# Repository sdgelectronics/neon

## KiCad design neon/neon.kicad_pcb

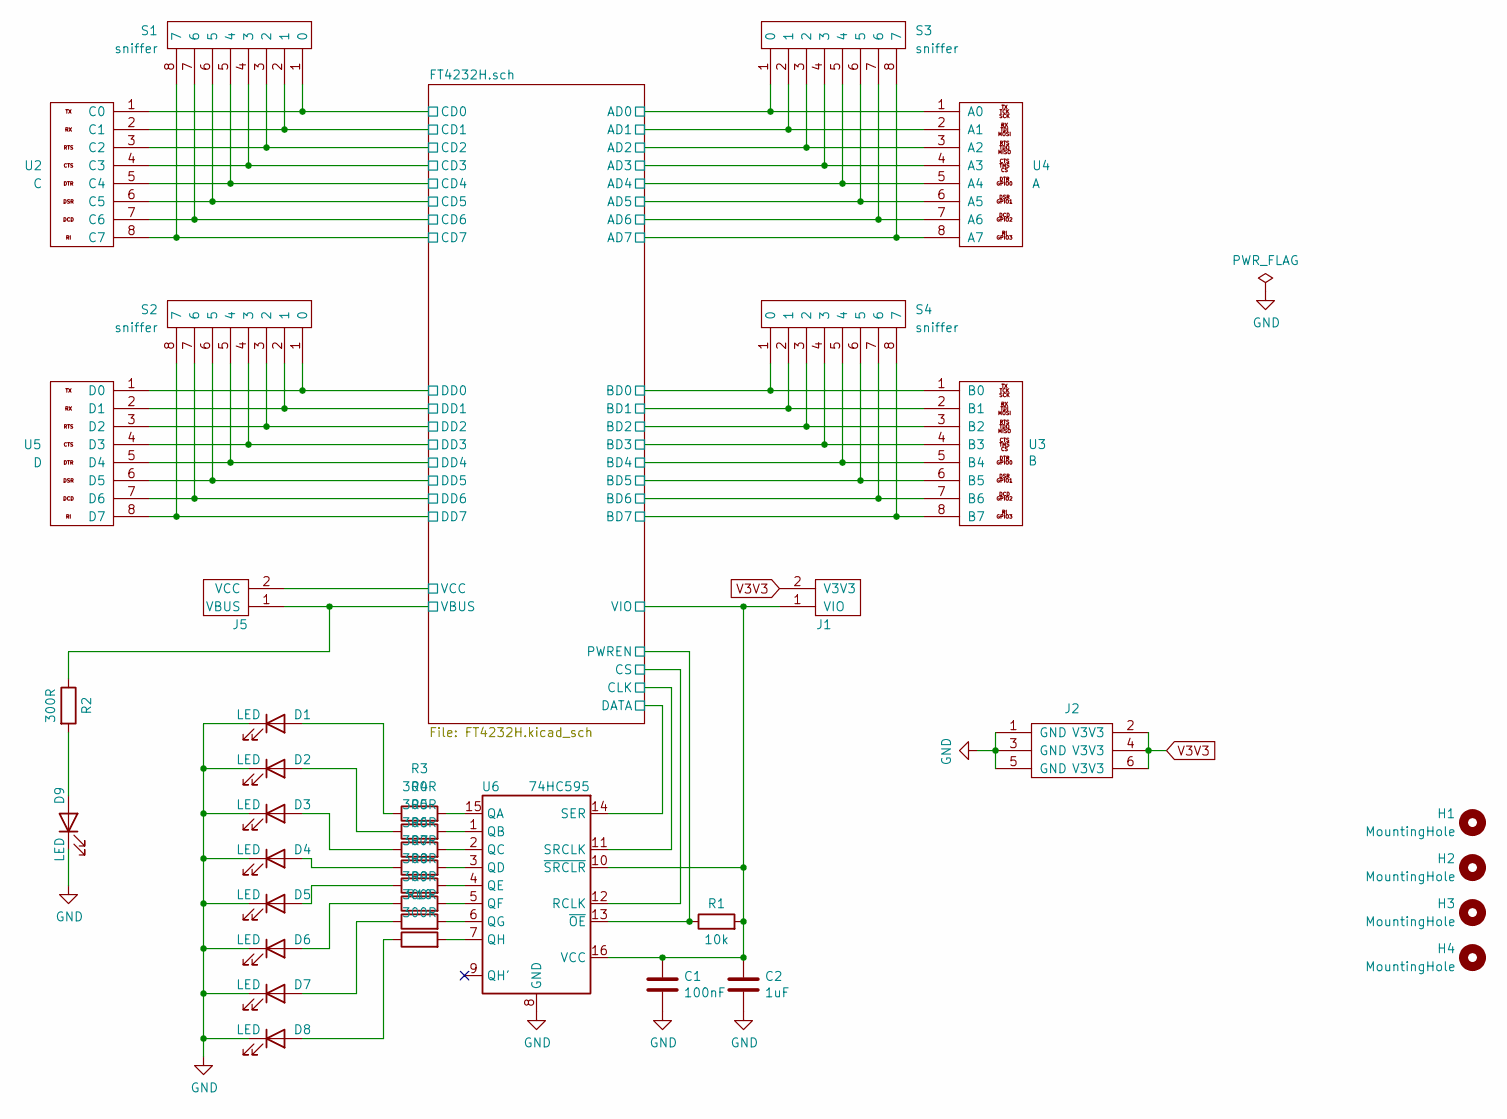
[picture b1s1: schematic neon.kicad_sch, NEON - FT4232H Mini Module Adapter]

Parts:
C1: 100nF; C_0805_2012Metric
C2: 1uF; C_0805_2012Metric
D1, D2, D3, D4, D5, D6, D7, D8, D9: LED; LED_0805_2012Metric
H1, H2, H3, H4: MountingHole; MountingHole_3.2mm_M3
J1: V3V3-VIO; PinHeader_1x02_P2.54mm_Vertical
J2: 3xV3V3-GND; PinHeader_2x03_P2.54mm_Vertical
J5: VBUS-VCC; PinHeader_1x02_P2.54mm_Vertical
R1: 10k; R_0805_2012Metric
R2: 300R; R_0805_2012Metric
R3, R4, R5, R6, R7, R8, R9, R10: 300R; R_0805_2012Metric_Pad1.20x1.40mm_HandSolder
S1, S2, S3, S4: sniffer; PinHeader_1x08_P2.54mm_Vertical
U2: C; PinHeader_1x08_P2.54mm_Vertical
U3: B; PinHeader_1x08_P2.54mm_Vertical
U4: A; PinHeader_1x08_P2.54mm_Vertical
U5: D; PinHeader_1x08_P2.54mm_Vertical
U6: 74HC595; SOIC-16_3.9x9.9mm_P1.27mm

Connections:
/AD0: S3.1 (0), U4.1 (A0); also elsewhere on the board
/AD1: S3.2 (1), U4.2 (A1); also elsewhere on the board
/AD2: S3.3 (2), U4.3 (A2); also elsewhere on the board
/AD3: S3.4 (3), U4.4 (A3); also elsewhere on the board
/AD4: S3.5 (4), U4.5 (A4); also elsewhere on the board
/AD5: S3.6 (5), U4.6 (A5); also elsewhere on the board
/AD6: S3.7 (6), U4.7 (A6); also elsewhere on the board
/AD7: S3.8 (7), U4.8 (A7); also elsewhere on the board
/BD0: S4.1 (0), U3.1 (B0); also elsewhere on the board
/BD1: S4.2 (1), U3.2 (B1); also elsewhere on the board
/BD2: S4.3 (2), U3.3 (B2); also elsewhere on the board
/BD3: S4.4 (3), U3.4 (B3); also elsewhere on the board
/BD4: S4.5 (4), U3.5 (B4); also elsewhere on the board
/BD5: S4.6 (5), U3.6 (B5); also elsewhere on the board
/BD6: S4.7 (6), U3.7 (B6); also elsewhere on the board
/BD7: S4.8 (7), U3.8 (B7); also elsewhere on the board
/CD0: S1.1 (0), U2.1 (C0); also elsewhere on the board
/CD1: S1.2 (1), U2.2 (C1); also elsewhere on the board
/CD2: S1.3 (2), U2.3 (C2); also elsewhere on the board
/CD3: S1.4 (3), U2.4 (C3); also elsewhere on the board
/CD4: S1.5 (4), U2.5 (C4); also elsewhere on the board
/CD5: S1.6 (5), U2.6 (C5); also elsewhere on the board
/CD6: S1.7 (6), U2.7 (C6); also elsewhere on the board
/CD7: S1.8 (7), U2.8 (C7); also elsewhere on the board
/CLK: U6.11 (SRCLK); also elsewhere on the board
/CS: U6.12 (RCLK); also elsewhere on the board
/DATA: U6.14 (SER); also elsewhere on the board
/DD0: S2.1 (0), U5.1 (D0); also elsewhere on the board
/DD1: S2.2 (1), U5.2 (D1); also elsewhere on the board
/DD2: S2.3 (2), U5.3 (D2); also elsewhere on the board
/DD3: S2.4 (3), U5.4 (D3); also elsewhere on the board
/DD4: S2.5 (4), U5.5 (D4); also elsewhere on the board
/DD5: S2.6 (5), U5.6 (D5); also elsewhere on the board
/DD6: S2.7 (6), U5.7 (D6); also elsewhere on the board
/DD7: S2.8 (7), U5.8 (D7); also elsewhere on the board
/PWREN: R1.1, U6.13 (~OE); also elsewhere on the board
/VBUS: J5.1 (VBUS), R2.1; also elsewhere on the board
/VCC: J5.2 (VCC); also elsewhere on the board
/VIO: C1.1, C2.1, J1.1 (VIO), R1.2, U6.10 (~SRCLR), U6.16 (VCC); also elsewhere on the board
GND: C1.2, C2.2, D1.1 (K), D2.1 (K), D3.1 (K), D4.1 (K), D5.1 (K), D6.1 (K), D7.1 (K), D8.1 (K), D9.1 (K), J2.1 (GND), J2.3 (GND), J2.5 (GND), U6.8 (GND); also elsewhere on the board
unnamed: D1.2 (A), R3.1
unnamed: D2.2 (A), R4.1
unnamed: D3.2 (A), R5.1
unnamed: D4.2 (A), R6.1
unnamed: D5.2 (A), R7.1
unnamed: D6.2 (A), R8.1
unnamed: D7.2 (A), R9.1
unnamed: D8.2 (A), R10.1
unnamed: D9.2 (A), R2.2
unnamed: R3.2, U6.15 (QA)
unnamed: R4.2, U6.1 (QB)
unnamed: R5.2, U6.2 (QC)
unnamed: R6.2, U6.3 (QD)
unnamed: R7.2, U6.4 (QE)
unnamed: R8.2, U6.5 (QF)
unnamed: R9.2, U6.6 (QG)
unnamed: R10.2, U6.7 (QH)
V3V3: J1.2 (V3V3), J2.2 (V3V3), J2.4 (V3V3), J2.6 (V3V3); also elsewhere on the board
no_connect_63: U6.9 (QH')

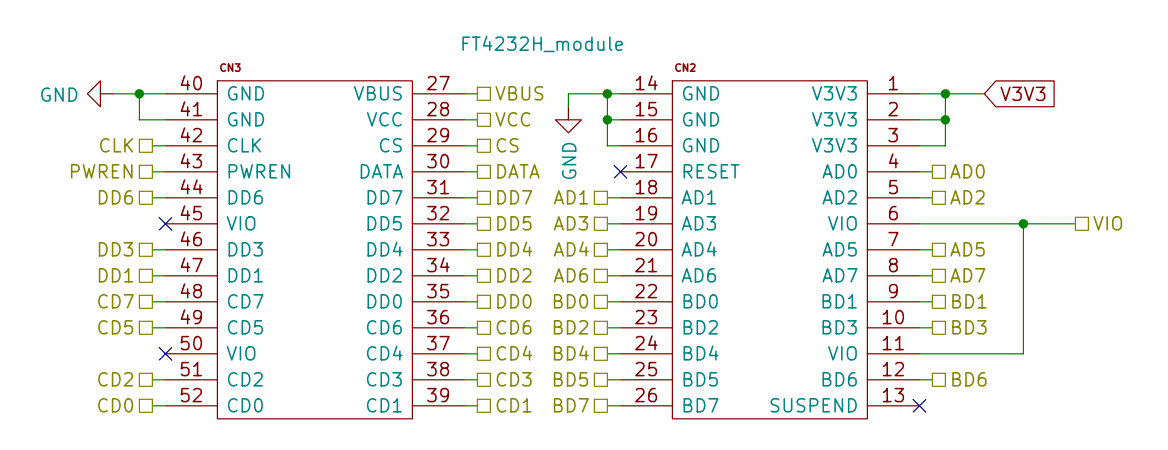
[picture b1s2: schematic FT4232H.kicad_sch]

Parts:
U1: FT4232H_module; FT4232H-MINI-MODULE-2

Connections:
/AD0: U1.4 (AD0); also elsewhere on the board
/AD1: U1.18 (AD1); also elsewhere on the board
/AD2: U1.5 (AD2); also elsewhere on the board
/AD3: U1.19 (AD3); also elsewhere on the board
/AD4: U1.20 (AD4); also elsewhere on the board
/AD5: U1.7 (AD5); also elsewhere on the board
/AD6: U1.21 (AD6); also elsewhere on the board
/AD7: U1.8 (AD7); also elsewhere on the board
/BD0: U1.22 (BD0); also elsewhere on the board
/BD1: U1.9 (BD1); also elsewhere on the board
/BD2: U1.23 (BD2); also elsewhere on the board
/BD3: U1.10 (BD3); also elsewhere on the board
/BD4: U1.24 (BD4); also elsewhere on the board
/BD5: U1.25 (BD5); also elsewhere on the board
/BD6: U1.12 (BD6); also elsewhere on the board
/BD7: U1.26 (BD7); also elsewhere on the board
/CD0: U1.52 (CD0); also elsewhere on the board
/CD1: U1.39 (CD1); also elsewhere on the board
/CD2: U1.51 (CD2); also elsewhere on the board
/CD3: U1.38 (CD3); also elsewhere on the board
/CD4: U1.37 (CD4); also elsewhere on the board
/CD5: U1.49 (CD5); also elsewhere on the board
/CD6: U1.36 (CD6); also elsewhere on the board
/CD7: U1.48 (CD7); also elsewhere on the board
/CLK: U1.42 (CLK); also elsewhere on the board
/CS: U1.29 (CS); also elsewhere on the board
/DATA: U1.30 (DATA); also elsewhere on the board
/DD0: U1.35 (DD0); also elsewhere on the board
/DD1: U1.47 (DD1); also elsewhere on the board
/DD2: U1.34 (DD2); also elsewhere on the board
/DD3: U1.46 (DD3); also elsewhere on the board
/DD4: U1.33 (DD4); also elsewhere on the board
/DD5: U1.32 (DD5); also elsewhere on the board
/DD6: U1.44 (DD6); also elsewhere on the board
/DD7: U1.31 (DD7); also elsewhere on the board
/PWREN: U1.43 (PWREN); also elsewhere on the board
/VBUS: U1.27 (VBUS); also elsewhere on the board
/VCC: U1.28 (VCC); also elsewhere on the board
/VIO: U1.6 (VIO), U1.11 (VIO); also elsewhere on the board
GND: U1.14 (GND), U1.15 (GND), U1.16 (GND), U1.40 (GND), U1.41 (GND); also elsewhere on the board
V3V3: U1.1 (V3V3), U1.2 (V3V3), U1.3 (V3V3); also elsewhere on the board
no_connect_59: U1.13 (SUSPEND)
no_connect_60: U1.17 (RESET)
no_connect_61: U1.45 (VIO)
no_connect_62: U1.50 (VIO)

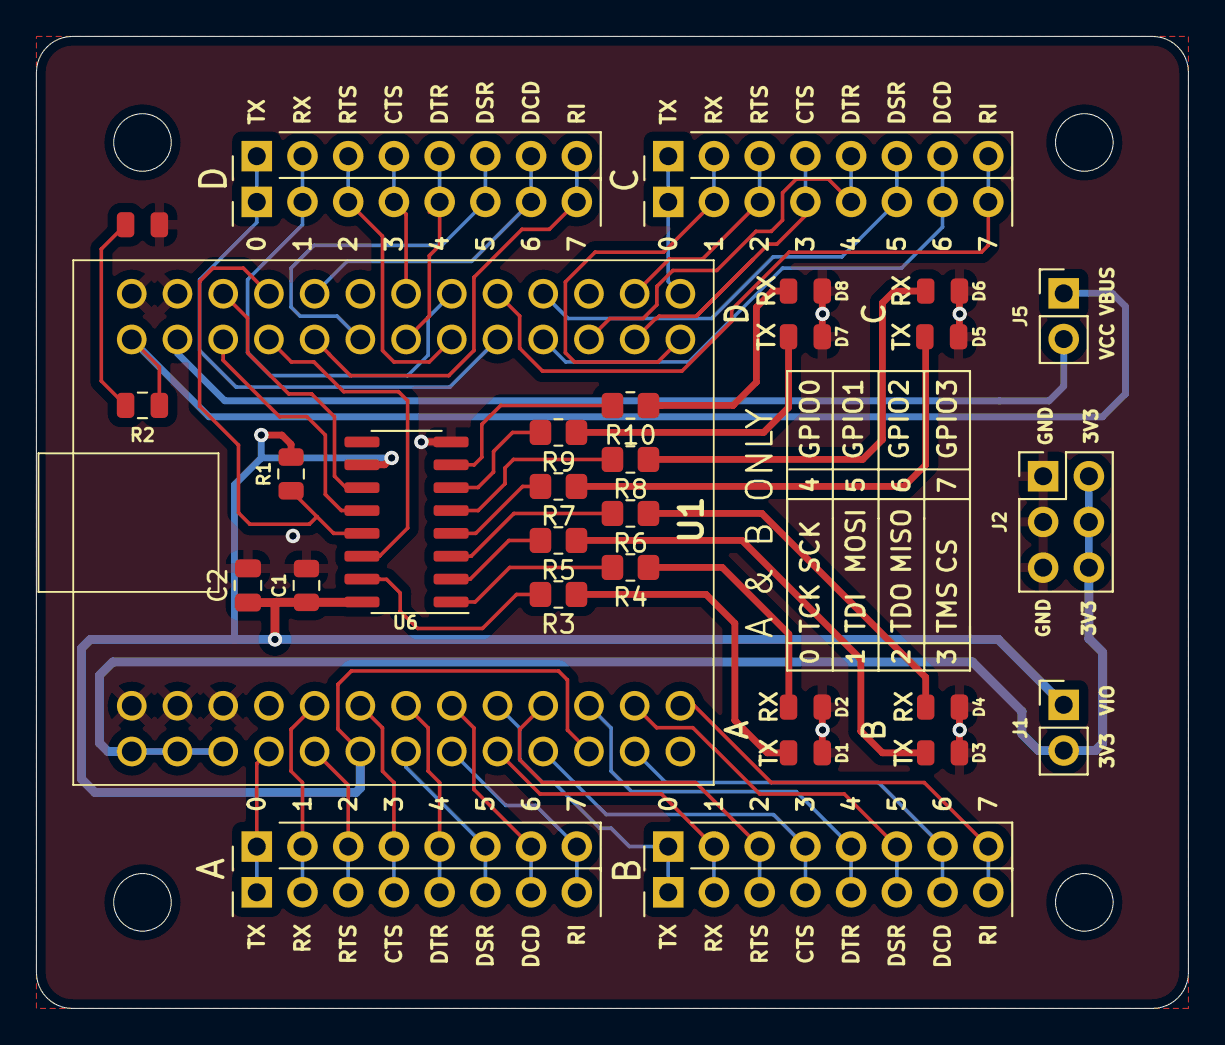
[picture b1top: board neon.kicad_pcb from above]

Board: 2 copper layers, 64.0 x 54.0 mm, 38 parts (0 on the bottom side), 58 nets.

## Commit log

2021-01-06 Minor modifications following data review
    Updated with updated copper pour, rounded edges. descrete resistors
